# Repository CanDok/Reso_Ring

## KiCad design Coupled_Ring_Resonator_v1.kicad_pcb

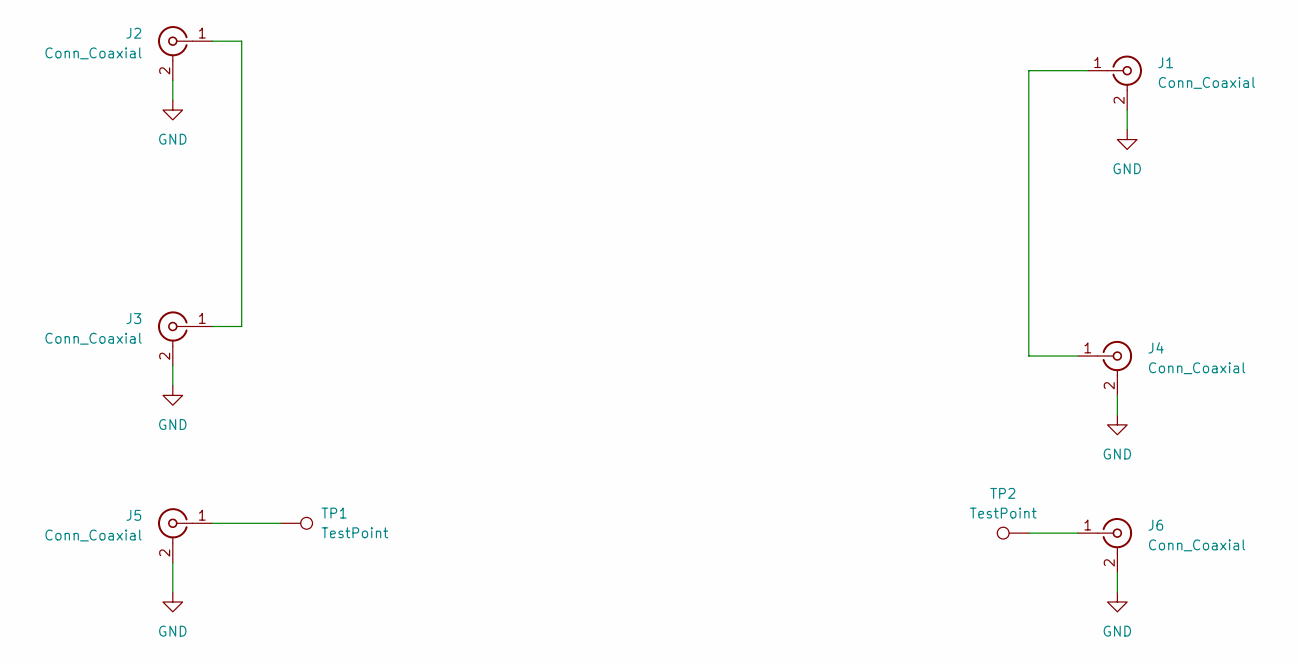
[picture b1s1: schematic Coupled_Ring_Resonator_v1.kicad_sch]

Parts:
J1, J2, J3, J4, J5, J6: Conn_Coaxial; SMA_Amphenol_132289_EdgeMount
TP1, TP2: TestPoint; TestPoint_Pad_3.0x3.0mm

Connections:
GND: J1.2 (Ext), J2.2 (Ext), J3.2 (Ext), J4.2 (Ext), J5.2 (Ext), J6.2 (Ext)
unnamed: J1.1 (In), J4.1 (In)
unnamed: J2.1 (In), J3.1 (In)
unnamed: J5.1 (In), TP1.1
unnamed: J6.1 (In), TP2.1

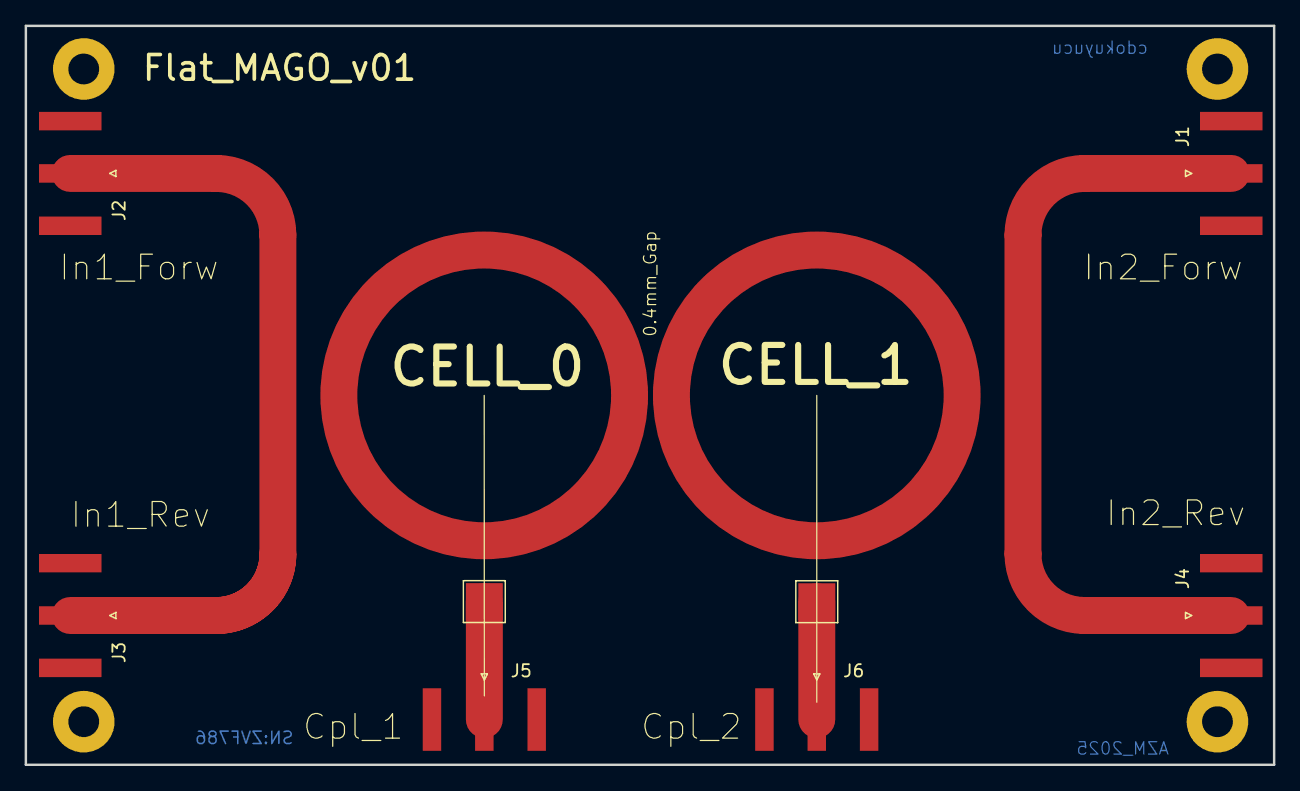
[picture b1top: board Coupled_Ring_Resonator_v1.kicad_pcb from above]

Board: 2 copper layers, 101.3 x 60.0 mm, 8 parts (0 on the bottom side), 5 nets.

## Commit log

2025-06-09 Add files via upload
    Coupled ring resonator rev1
